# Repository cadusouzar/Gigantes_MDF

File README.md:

# Gigantes de MDF

### Alunos ###

Carlos Eduardo de Souza Ribeiro - 174040

Alvaro Gochi de Sousa - 172158

Neemias Vieira Fernandes - 170550

João Victor Teixeira - 147653

# Sobre o Projeto:

O projeto Gigantes de MDF, vem com o intuito dos alunos aplicarem os conceitos recebidos pela disciplina de Programação de Hardware. O intuito é cada grupo criar seu código de um robô que dispara laser e também detecta laser recebido por meio de sensores. Os componentes utilizados no projeto foram:

- 1x Arduino Nano
- 1x Resistores de 10kohms
- 3x Resisrores de 360ohms
- 5x Botões
- 2x Motores DC
- 1x C.I de ponte H L293D
- 1x Diodo Laser
- 1x LDR de 20mm

O código foi desenvolvido na linguagem C utilizando apenas o ATMEGA328, foi utilizado o programa SimulIde para debugar o codigo, também o próprio programa Arduino para gravar no arduino e testar.

# Pinagem 

### Motores ###
- PD2 -> MOTOR ESQUERDO "FRENTE"
- PD3 -> MOTOR ESQUERDO "TRAS"
- PD4 -> MOTOR DIREITO "FRENTE"
- PD5 -> MOTOR PWM ESQUERDO
- PD6 -> MOTOR PWM DIREITO
- PD7 -> MOTOR DIREITO "TRAS"

### Leds ###

- PC5 -> LED 
- PC3 -> LED
- PC2 -> LED
- PC1 -> DIODO LASER (ELE PRECISA FICAR EM LOOP, SOLTANDO LASER A CADA 1 SEGUNDO AUTOMATICAMENTE)

### Sensores ###

- PCO -> LDR

### Botões ###

- PBO -> BOTAO ANDAR PRA FRENTE (GIRA OS DOIS MOTORES PRA FRENTE)
- PB1 -> BOTAO (APENAS RODA DA DIREITA GIRA PRA FRENTE)
- PB2 -> BOTAO (APENAS RODA DA ESQUERDA GIRA PRA FRENTE)
- PB3 -> BOTAO ALTERNA PARA RÉ, FAZENDO COM QUE OS BOTOES ANTERIORES GIREM AS RODAS PARA TRAS NA DETERMINADA LOGICA: AO CLICAR ESSE BOTAO PB0 GIRA AS DUAS PARA TRAS, PB1 GIRA APENAS A RODA DA DIREITA PARA TRAS E PB2 GIRA - APENAS A RODA DA ESQUERDA PARA TRAS
- PB4 -> BOTAO PARA LIGAR OS LEDS (REINICIA AS VIDAS)

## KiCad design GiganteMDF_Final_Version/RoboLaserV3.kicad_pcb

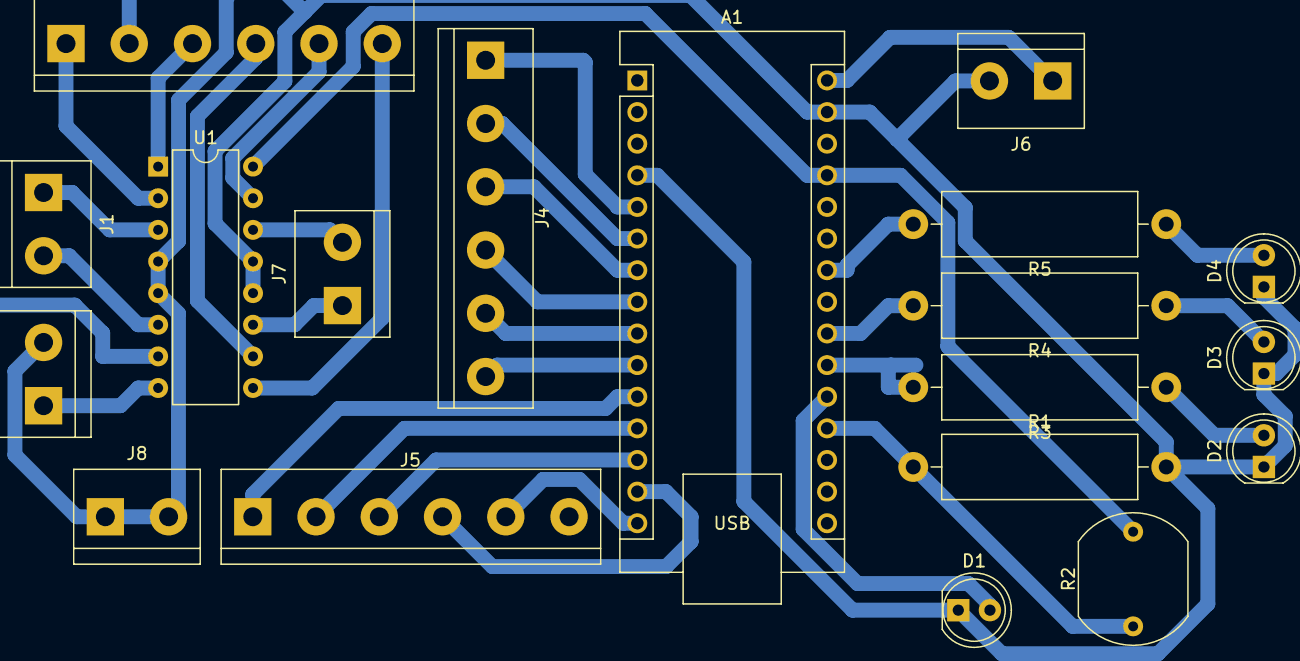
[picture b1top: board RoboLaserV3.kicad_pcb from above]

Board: 2 copper layers, 19 parts (0 on the bottom side), 33 nets.

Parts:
A1: Arduino_Nano_v3.x; Arduino_Nano
D1: LASER; LED_D5.0mm
D2: VIDA 1; LED_D5.0mm
D3: VIDA 2; LED_D5.0mm
D4: VIDA 3; LED_D5.0mm
J1, J2, J6, J7, J8: Screw_Terminal_01x02; TerminalBlock_bornier-2_P5.08mm
J3, J4, J5: Screw_Terminal_01x06; TerminalBlock_bornier-6_P5.08mm
R1, R3, R4, R5: R; R_Axial_DIN0516_L15.5mm_D5.0mm_P20.32mm_Horizontal
R2: LDR03; R_LDR_10x8.5mm_P7.6mm_Vertical
U1: L293D; DIP-16_W7.62mm

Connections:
1Y: J1.1, U1.3 (1Y)
2Y: J1.2, U1.6 (2Y)
3Y: J7.1, U1.11 (3Y)
4Y: J7.2, U1.14 (4Y)
5V: A1.27 (+5V), R2.2, U1.16 (VCC1)
A0: A1.19 (A0), R1.1, R2.1
A1: A1.20 (A1), D1.2 (A)
A2: A1.21 (A2), R3.2
A3: A1.22 (A3), R4.2
A6: A1.24 (A5), R5.2
BORN SAIDA ARDUINO 1: A1.5 (D2), J4.1
BORN SAIDA ARDUINO 2: A1.6 (D3), J4.2
BORN SAIDA ARDUINO 3: A1.7 (D4), J4.3
BORN SAIDA ARDUINO 4: A1.8 (D5), J4.4
BORN SAIDA ARDUINO 5: A1.9 (D6), J4.5
BORN SAIDA ARDUINO 6: A1.10 (D7), J4.6
BORN SAIDA ARDUINO 7: A1.11 (D8), J5.1
BORN SAIDA ARDUINO 8: A1.12 (D9), J5.2
BORN SAIDA ARDUINO 9: A1.13 (D10), J5.3
BORN SAIDA ARDUINO 10: A1.14 (D11), J5.4
BORN SAIDA ARDUINO 11: A1.15 (D12), J5.5
BORNE ENTRADA CI 1: J3.1, U1.2 (1A)
BORNE ENTRADA CI 2: J3.2, U1.7 (2A)
BORNE ENTRADA CI 3: J3.3, U1.1 (EN1,2)
BORNE ENTRADA CI 4: J3.4, U1.10 (3A)
BORNE ENTRADA CI 5: J3.5, U1.15 (4A)
BORNE ENTRADA CI 6: J3.6, U1.9 (EN3,4)
GND: A1.4 (GND), A1.29 (GND), D1.1 (K), D2.1 (K), D3.1 (K), D4.1 (K), J2.2, J6.2, J8.1, J8.2, R1.2, U1.4 (GND), U1.5 (GND), U1.12 (GND), U1.13 (GND)
unnamed: D2.2 (A), R3.1
unnamed: D3.2 (A), R4.1
unnamed: D4.2 (A), R5.1
unnamed: J2.1, U1.8 (VCC2)
VIN: A1.30 (VIN), J6.1

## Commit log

2024-11-23 Codigo C
    Codigo C para funcionar o Gigante de MDF
2024-11-23 Circuito Kicad versão final
    Circuito feito no programa kicad para realização da pcb do projeto
2024-11-23 Codigo C
    Codigo feito em C para o funcionamento do projeto
2024-11-23 Codigo C
    Codigo em linguagem C para o funcionamento total do projeto
2024-11-23 Doxygen completo do codigo
2024-11-23 Circuito Kicad
    Circuito da PCB do projeto realizado no Kicad 8.0
